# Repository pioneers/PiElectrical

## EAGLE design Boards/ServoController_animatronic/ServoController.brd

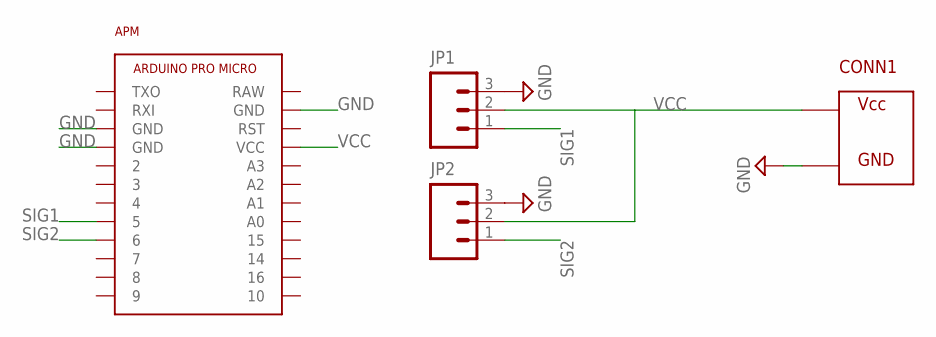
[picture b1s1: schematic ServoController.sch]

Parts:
APM: ARDUINO_PRO_MICRO
CONN1: ATX
JP1, JP2: M031X03-MTA; 1X03-MTA

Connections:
GND: APM.GND@0 (GND), APM.GND@1 (GND), APM.GND@2 (GND), CONN1.P$2, JP1.3, JP2.3
SIG1: APM.5, JP1.1
SIG2: APM.6, JP2.1
VCC: APM.VCC, CONN1.P$1, JP1.2, JP2.2

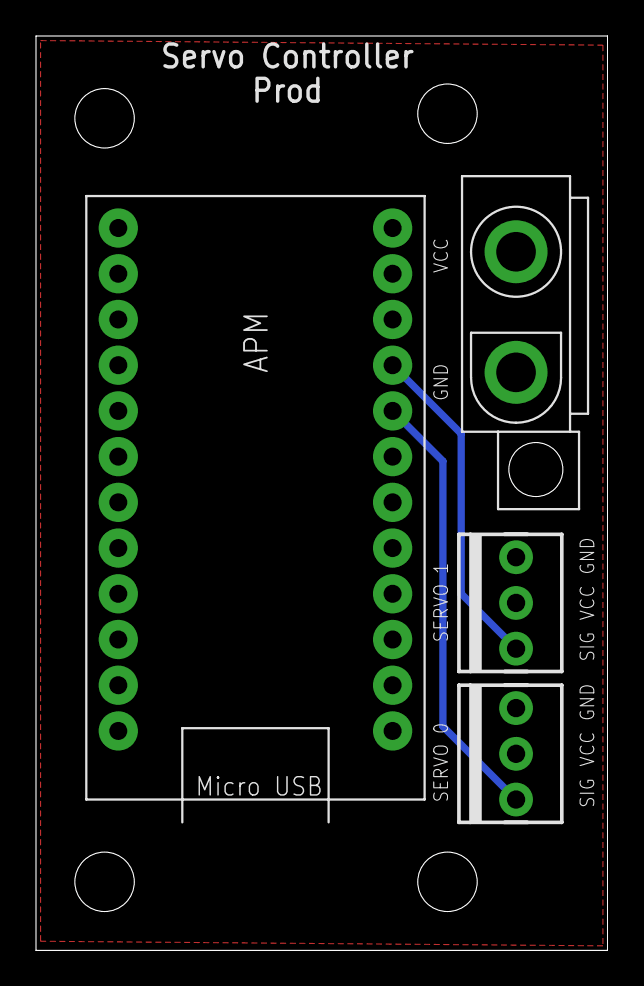
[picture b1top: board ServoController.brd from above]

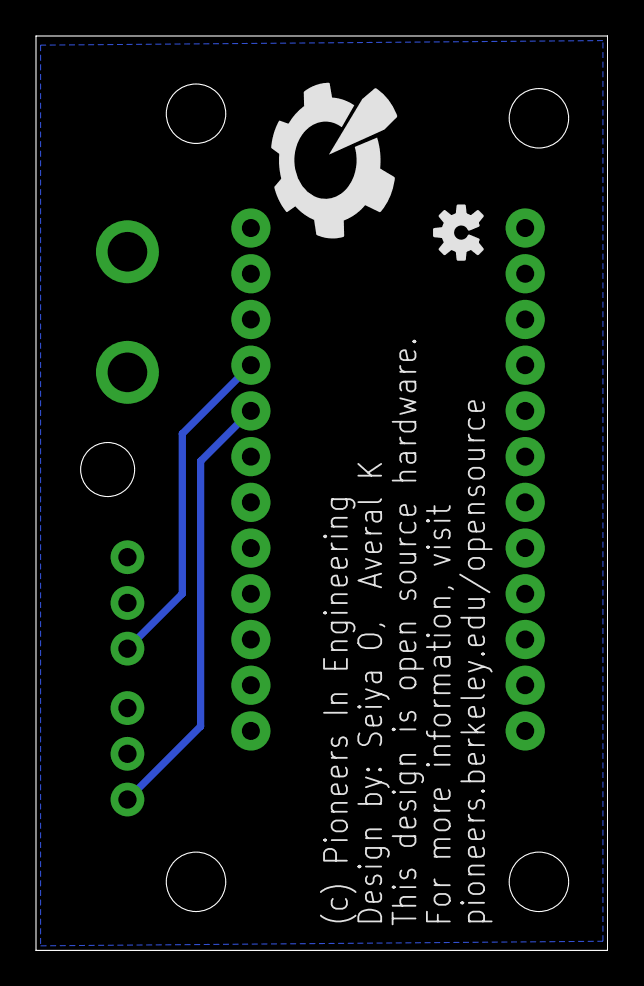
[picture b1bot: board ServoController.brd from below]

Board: 2 copper layers, 31.8 x 50.8 mm, 10 parts (2 on the bottom side), 4 nets.

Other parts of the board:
U$1, U$3, U$4, U$5: STAND-OFF
U$2: PIE-LOGO-SMALL
U$6: OSHW-LOGO-S

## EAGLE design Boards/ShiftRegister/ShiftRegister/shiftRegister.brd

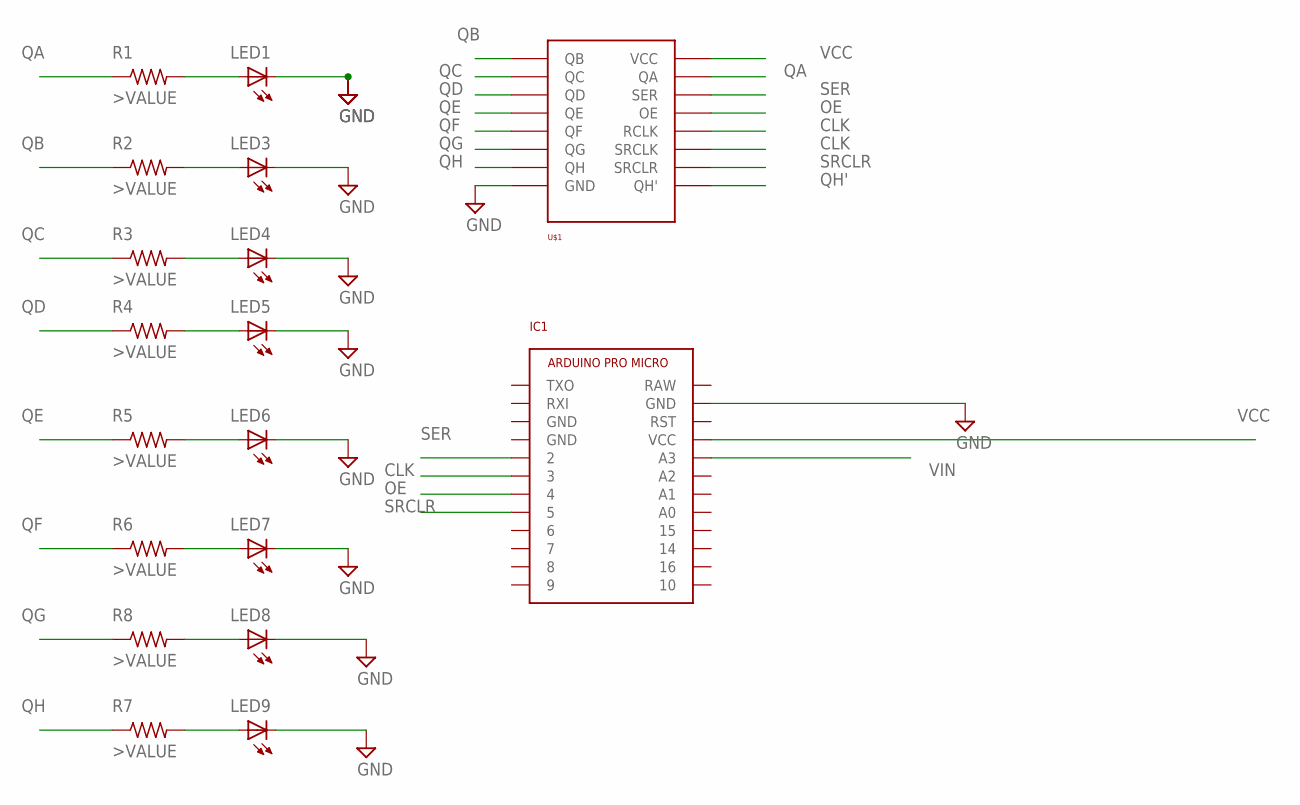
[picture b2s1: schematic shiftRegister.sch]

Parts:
IC1: ARDUINO_PRO_MICRO
LED1, LED3, LED4, LED5, LED6, LED7, LED8, LED9: LED-FKIT-1206; FKIT-LED-1206
R1, R2, R3, R4, R5, R6, R7, R8: >VALUE; R0603
U$1: SN74HC595

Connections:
CLK: IC1.3, U$1.RCLK, U$1.SRCLK
GND: IC1.GND@2 (GND), LED1.C, LED3.C, LED4.C, LED5.C, LED6.C, LED7.C, LED8.C, LED9.C, U$1.GND
unnamed: LED1.A, R1.2
unnamed: LED3.A, R2.2
unnamed: LED4.A, R3.2
unnamed: LED5.A, R4.2
unnamed: LED6.A, R5.2
unnamed: LED7.A, R6.2
unnamed: LED8.A, R8.2
unnamed: LED9.A, R7.2
OE: IC1.4, U$1.OE
QA: R1.1, U$1.QA
QB: R2.1, U$1.QB
QC: R3.1, U$1.QC
QD: R4.1, U$1.QD
QE: R5.1, U$1.QE
QF: R6.1, U$1.QF
QG: R8.1, U$1.QG
QH: R7.1, U$1.QH
QH': U$1.QH'
SER: IC1.2, U$1.SER
SRCLR: IC1.5, U$1.SRCLR
VCC: IC1.VCC, U$1.VCC
VIN: IC1.A3

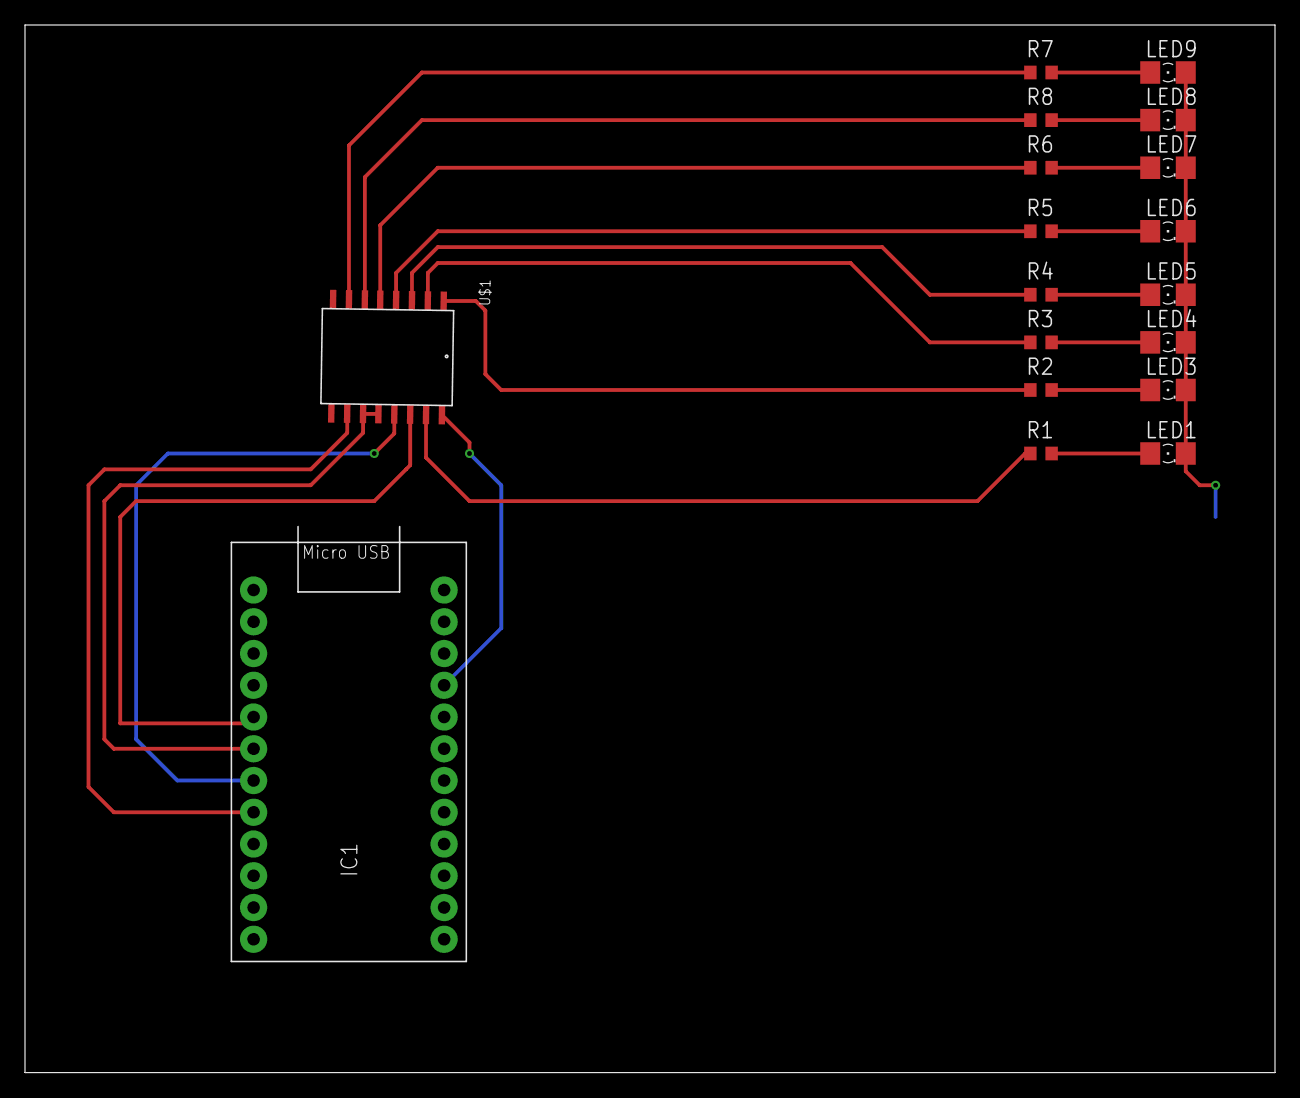
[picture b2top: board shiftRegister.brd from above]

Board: 2 copper layers, 100.0 x 83.8 mm, 18 parts (0 on the bottom side), 22 nets.

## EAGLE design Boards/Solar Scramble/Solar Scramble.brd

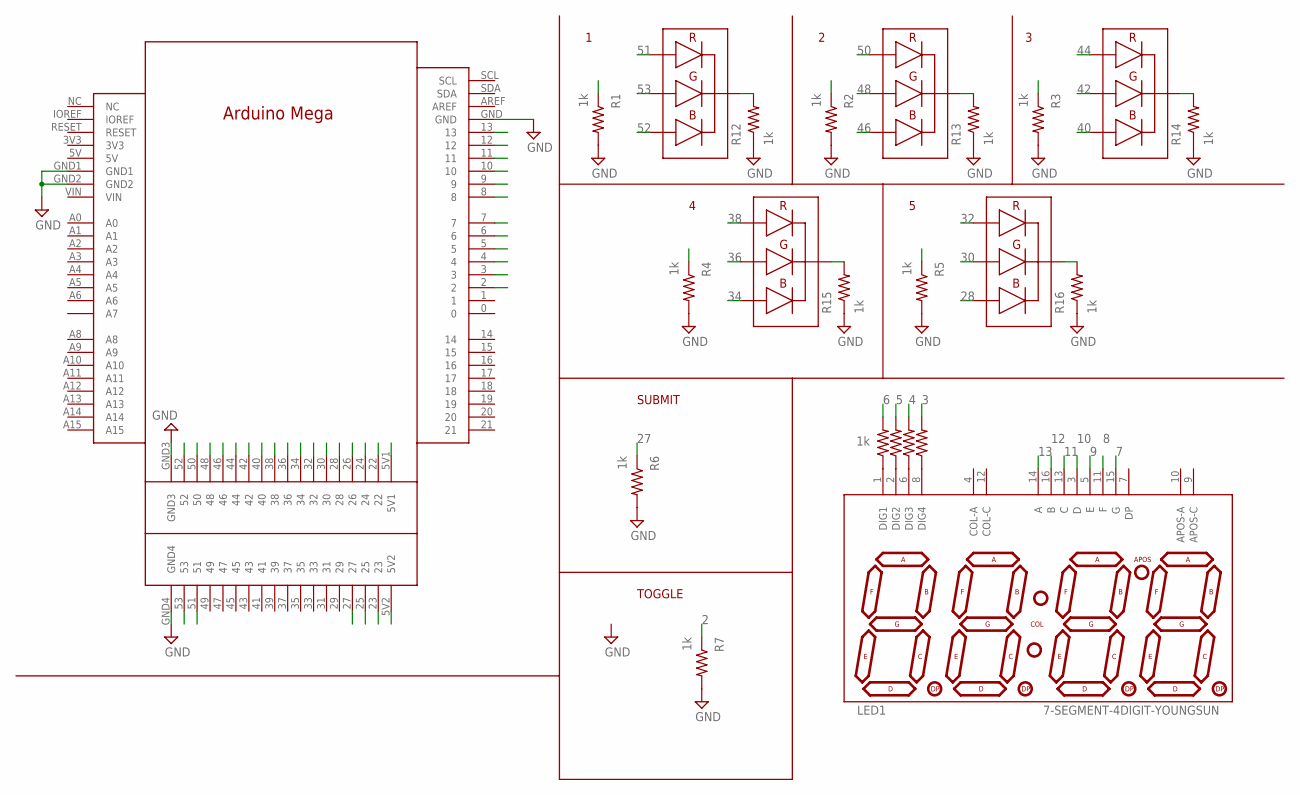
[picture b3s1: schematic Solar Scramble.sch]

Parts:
LED1: 7-SEGMENT-4DIGIT-YOUNGSUN
R1, R2, R3, R4, R5, R6, R7, R9, R10, R11, R12, R13, R14, R15, R16: 1k; R0603
R8: 1ik; R0603
U$1: ARD_MEGA
U$2, U$3, U$4, U$5, U$6: TRI-LED

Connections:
2: R7.1, U$1.2
3: R11.2, U$1.3
4: R10.2, U$1.4
5: R9.2, U$1.5
5V: U$1.5V1, U$1.5V2
6: R8.2, U$1.6
7: LED1.15 (G), U$1.7
8: LED1.11 (F), U$1.8
9: LED1.5 (E), U$1.9
10: LED1.3 (D), U$1.10
11: LED1.13 (C), U$1.11
12: LED1.16 (B), U$1.12
13: LED1.14 (A), U$1.13
22: R1.1, U$1.22
23: R2.1, U$1.23
24: R3.1, U$1.24
25: R4.1, U$1.25
26: R5.1, U$1.26
27: R6.1, U$1.27
28: U$1.28, U$5.B
30: U$1.30, U$5.G
32: U$1.32, U$5.R
34: U$1.34, U$4.B
36: U$1.36, U$4.G
38: U$1.38, U$4.R
40: U$1.40, U$3.B
42: U$1.42, U$3.G
44: U$1.44, U$3.R
46: U$1.46, U$6.B
48: U$1.48, U$6.G
50: U$1.50, U$6.R
51: U$1.51, U$2.R
52: U$1.52, U$2.B
53: U$1.53, U$2.G
GND: R1.2, R2.2, R3.2, R4.2, R5.2, R6.2, R7.2, R12.1, R13.1, R14.1, R15.1, R16.1, U$1.GND, U$1.GND1, U$1.GND2, U$1.GND3, U$1.GND4
unnamed: R15.2, U$4.GND (CAT)
unnamed: R12.2, U$2.GND (CAT)
unnamed: LED1.1 (DIG1), R8.1
unnamed: LED1.2 (DIG2), R9.1
unnamed: LED1.6 (DIG3), R10.1
unnamed: LED1.8 (DIG4), R11.1
unnamed: R13.2, U$6.GND (CAT)
unnamed: R14.2, U$3.GND (CAT)
unnamed: R16.2, U$5.GND (CAT)

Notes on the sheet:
SUBMIT
TOGGLE

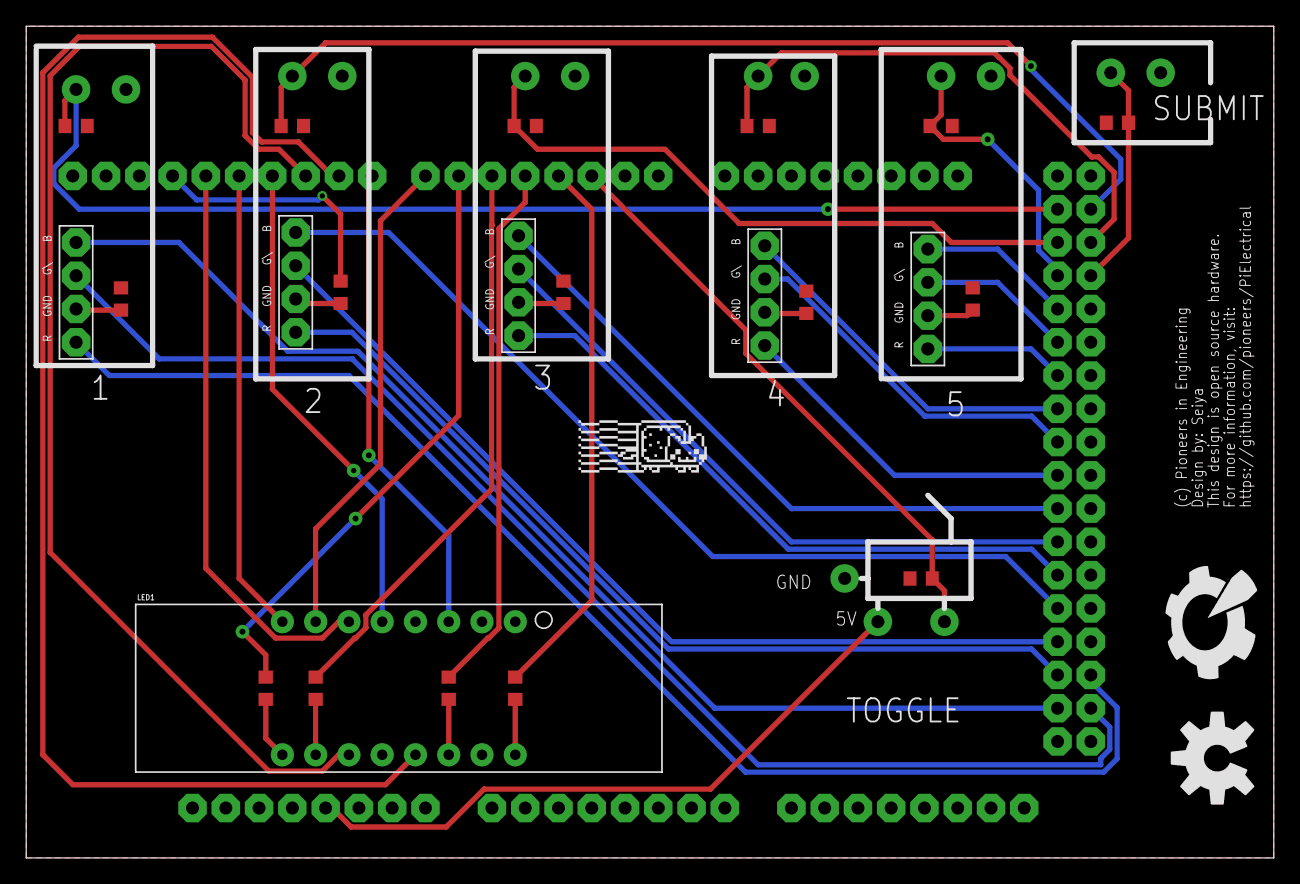
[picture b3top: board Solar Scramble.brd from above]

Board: 2 copper layers, 95.2 x 63.5 mm, 26 parts (0 on the bottom side), 44 nets.

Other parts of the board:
U$7: NYAN-1CM
U$8: OSHW-LOGO-L
U$9: PIE-LOGO-SMALL

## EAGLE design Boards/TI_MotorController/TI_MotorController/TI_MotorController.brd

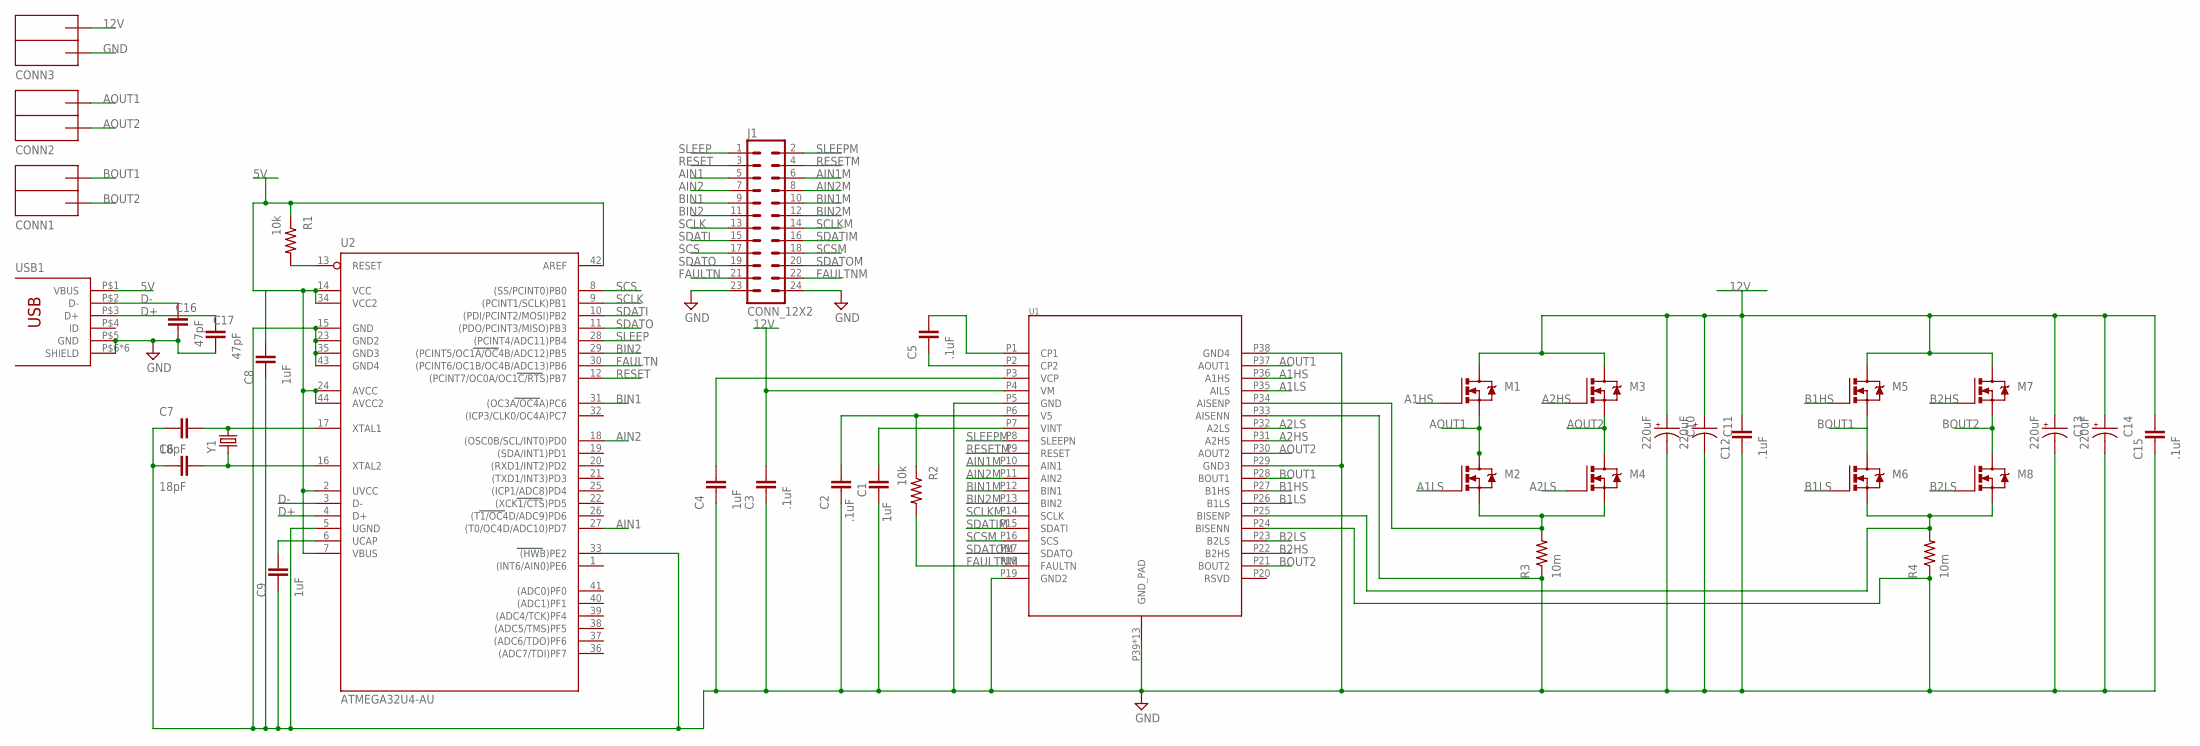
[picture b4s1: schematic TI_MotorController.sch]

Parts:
C1, C4, C8, C9: 1uF; 0603-CAP
C2, C3, C5, C12, C15: .1uF; 0603-CAP
C6, C7: 18pF; 0603-CAP
C10, C11, C13, C14: 220uF; NIPPON_F80
C16, C17: 47pF; 0603-CAP
CONN1, CONN2, CONN3: ANDERSONVERTICAL; ANDERSON_VERTICAL
J1: CONN_12X2; 2X12
M1, M2, M3, M4, M5, M6, M7, M8: NMOS_CSD17579Q3A; DNH0008A
R1, R2: 10k; R0603
R3, R4: 10m; R2512
U1: DRV8704; HTSSOP(38)
U2: ATMEGA32U4-AU; TQFP44
USB1: USB-OTGMICRO-AB; USB-MICRO-AB
Y1: CRYSTAL10.5X4.8; CRYSTAL-SMD-10.5X4.8-2PIN

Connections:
5V: C8.2, R1.1, U2.2 (UVCC), U2.7 (VBUS), U2.14 (VCC), U2.24 (AVCC), U2.34 (VCC2), U2.42 (AREF), U2.44 (AVCC2), USB1.P$1 (VBUS)
12V: C3.2, C10.+, C11.+, C12.2, C13.+, C14.+, C15.2, CONN3.PIN1 (OUTB), M1.5 (D), M1.6 (D), M1.7 (D), M1.8 (D), M1.9 (D), M3.5 (D), M3.6 (D), M3.7 (D), M3.8 (D), M3.9 (D), M5.5 (D), M5.6 (D), M5.7 (D), M5.8 (D), M5.9 (D), M7.5 (D), M7.6 (D), M7.7 (D), M7.8 (D), M7.9 (D), U1.P4 (VM)
A1HS: M1.4 (G), U1.P36 (A1HS)
A1LS: M2.4 (G), U1.P35 (AILS)
A2HS: M3.4 (G), U1.P31 (A2HS)
A2LS: M4.4 (G), U1.P32 (A2LS)
AIN1: J1.5, U2.27 ((T0/OC4D/ADC10)PD7)
AIN1M: J1.6, U1.P10 (AIN1)
AIN2: J1.7, U2.18 ((OSC0B/SCL/INT0)PD0)
AIN2M: J1.8, U1.P11 (AIN2)
AOUT1: CONN2.PIN1 (OUTB), M1.1 (S), M1.2 (S), M1.3 (S), M2.5 (D), M2.6 (D), M2.7 (D), M2.8 (D), M2.9 (D), U1.P37 (AOUT1)
AOUT2: CONN2.PIN2 (OUTA), M3.1 (S), M3.2 (S), M3.3 (S), M4.5 (D), M4.6 (D), M4.7 (D), M4.8 (D), M4.9 (D), U1.P30 (AOUT2)
B1HS: M5.4 (G), U1.P27 (B1HS)
B1LS: M6.4 (G), U1.P26 (B1LS)
B2HS: M7.4 (G), U1.P22 (B2HS)
B2LS: M8.4 (G), U1.P23 (B2LS)
BIN1: J1.9, U2.31 ((OC3A/OC4A)PC6)
BIN1M: J1.10, U1.P12 (BIN1)
BIN2: J1.11, U2.29 ((PCINT5/OC1A/OC4B/ADC12)PB5)
BIN2M: J1.12, U1.P13 (BIN2)
BOUT1: CONN1.PIN1 (OUTB), M5.1 (S), M5.2 (S), M5.3 (S), M6.5 (D), M6.6 (D), M6.7 (D), M6.8 (D), M6.9 (D), U1.P28 (BOUT1)
BOUT2: CONN1.PIN2 (OUTA), M7.1 (S), M7.2 (S), M7.3 (S), M8.5 (D), M8.6 (D), M8.7 (D), M8.8 (D), M8.9 (D), U1.P21 (BOUT2)
D+: C17.2, U2.4 (D+), USB1.P$3 (D+)
D-: C16.2, U2.3 (D-), USB1.P$2 (D-)
FAULTN: J1.21, U2.30 ((PCINT6/OC1B/OC4B/ADC13)PB6)
FAULTNM: J1.22, R2.2, U1.P18 (FAULTN)
GND: C1.1, C2.1, C3.1, C4.1, C6.1, C7.1, C8.1, C9.1, C10.-, C11.-, C12.1, C13.-, C14.-, C15.1, C16.1, C17.1, CONN3.PIN2 (OUTA), J1.23, J1.24, R3.1, R4.1, U1.P5 (GND), U1.P19 (GND2), U1.P24 (BISENN), U1.P29 (GND3), U1.P33 (AISENN), U1.P38 (GND4), U1.P39 (GND_PAD), U1.P40 (GND_PAD), U1.P41 (GND_PAD), U1.P42 (GND_PAD), U1.P43 (GND_PAD), U1.P44 (GND_PAD), U1.P45 (GND_PAD), U1.P46 (GND_PAD), U1.P47 (GND_PAD), U1.P48 (GND_PAD), U1.P49 (GND_PAD), U1.P50 (GND_PAD), U1.P51 (GND_PAD), U2.5 (UGND), U2.15 (GND), U2.23 (GND2), U2.33 ((HWB)PE2), U2.35 (GND3), U2.43 (GND4), USB1.P$5 (GND), USB1.P$6 (SHIELD), USB1.P$7 (SHIELD), USB1.P$8 (SHIELD), USB1.P$9 (SHIELD), USB1.P$10 (SHIELD), USB1.P$11 (SHIELD)
unnamed: C1.2, U1.P7 (VINT)
unnamed: C2.2, R2.1, U1.P6 (V5)
unnamed: R1.2, U2.13 (RESET)
unnamed: C4.2, U1.P3 (VCP)
unnamed: C5.1, U1.P2 (CP2)
unnamed: C5.2, U1.P1 (CP1)
unnamed: C7.2, U2.17 (XTAL1), Y1.P$2 (2)
unnamed: C6.2, U2.16 (XTAL2), Y1.P$1 (1)
unnamed: C9.2, U2.6 (UCAP)
unnamed: M2.1 (S), M2.2 (S), M2.3 (S), M4.1 (S), M4.2 (S), M4.3 (S), R3.2, U1.P34 (AISENP)
unnamed: M6.1 (S), M6.2 (S), M6.3 (S), M8.1 (S), M8.2 (S), M8.3 (S), R4.2, U1.P25 (BISENP)
RESET: J1.3, U2.12 ((PCINT7/OC0A/OC1C/RTS)PB7)
RESETM: J1.4, U1.P9 (RESET)
SCLK: J1.13, U2.9 ((PCINT1/SCLK)PB1)
SCLKM: J1.14, U1.P14 (SCLK)
SCS: J1.17, U2.8 ((SS/PCINT0)PB0)
SCSM: J1.18, U1.P16 (SCS)
SDATI: J1.15, U2.10 ((PDI/PCINT2/MOSI)PB2)
SDATIM: J1.16, U1.P15 (SDATI)
SDATO: J1.19, U2.11 ((PDO/PCINT3/MISO)PB3)
SDATOM: J1.20, U1.P17 (SDATO)
SLEEP: J1.1, U2.28 ((PCINT4/ADC11)PB4)
SLEEPM: J1.2, U1.P8 (SLEEPN)

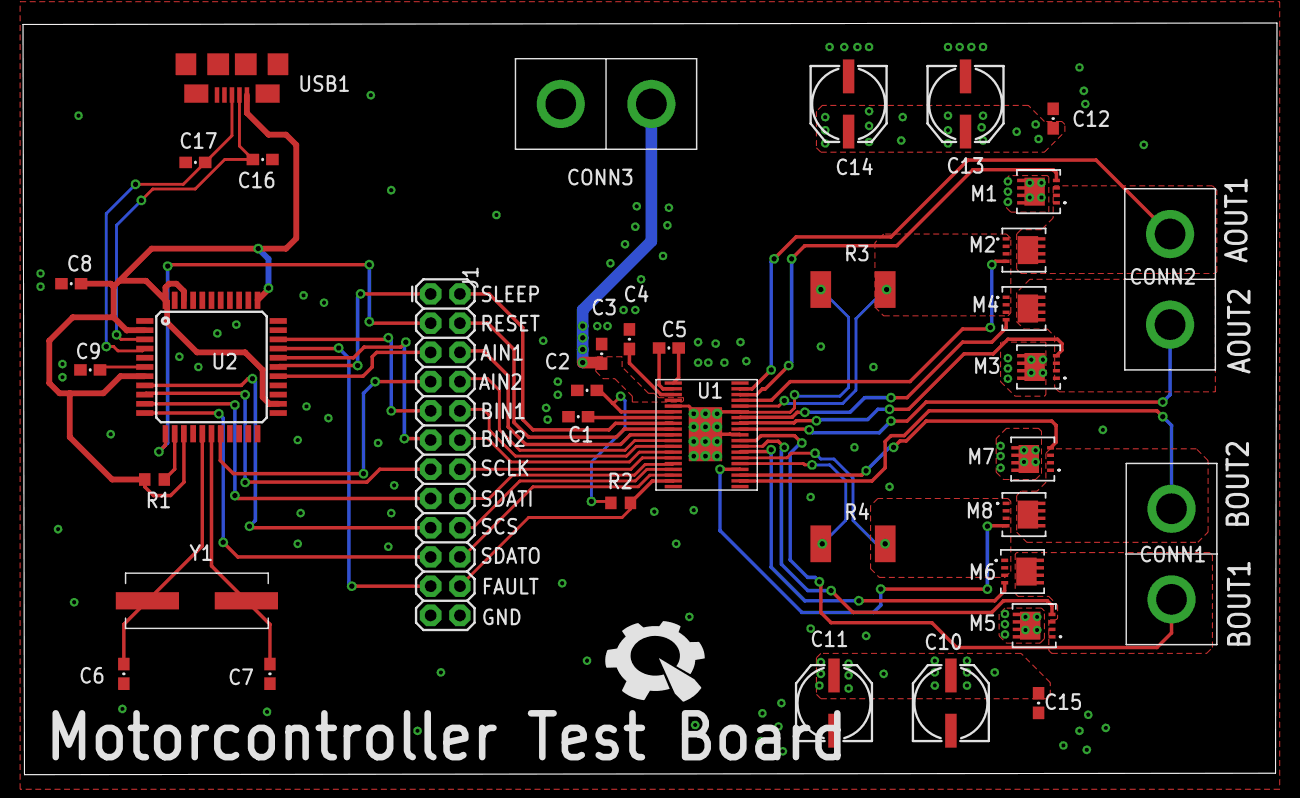
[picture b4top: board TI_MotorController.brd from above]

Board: 2 copper layers, 109.0 x 65.3 mm, 38 parts (0 on the bottom side), 50 nets.

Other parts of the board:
U$1: PIE-LOGO-SMALL

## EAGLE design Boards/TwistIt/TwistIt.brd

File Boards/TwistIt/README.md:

# TwistIt

Screw terminal based potentiometer/line follower/limit switch ultimate board

Named TwistIt for the screw terminal (open to suggestions)

Digital in Pins are all labeled "Arduino" in the pinout diagram

Analog pins are labeled as such

Analog pins can be used as digital, NOT vice versa

[2 Pin](https://www.sparkfun.com/products/8432) [3 pin](https://www.sparkfun.com/products/8433)

## Reed switches

Basically when it is placed in a magnetic field, the switch closes.

There surface mounts and through hole variants, but generally they have the same working range

For more specs, please view the link below:

http://www.digikey.com/product-search/en/switches/magnetic-reed-switches/1114199

It can be bought from Digikey, Sparkfun, Aliexpress, Amazon.

[AliExpress](https://www.aliexpress.com/item/10pcs-KSK-1A-Reed-Switch-2x14mm-Green-Glass-Usually-Open-For-Sensors-100-Original/32424207994.html)

To test it, connect it in series with a resistor and take the input from the point between them.

A sample of a simple code is shown below:

```
int reed = 2;

int LED = 3;

void setup() {

Serial.begin(9600);

pinMode(reed,INPUT);

pinMode(LED,OUTPUT);

}

void loop() {

if(digitalRead(reed)==HIGH){

digitalWrite(LED, HIGH);

}

else digitalWrite(3, LOW);

}
```
where an LED is attached to pin 3.

## Yogi Bear Break Out

VNH2SP30 | APM
-------- | ---
5V | Vcc
GND | GND
EN | 14
INA | 16
INB | 10
CS | 8
PMW | 9
Encoder A | 2
Encoder B | 3
Red | 4
Yellow | 5
Green | 6

[New Motor 1](https://e-smotor.en.alibaba.com/product/60220884310-801307434/37GB_spur_gear_motor_with_encoder.html?spm=a2700.7803228.1998738836.575.wFZGi0)

[New Motor 2](https://jslmotor.en.alibaba.com/product/60311538644-211952029/12v_24v_Pure_Metal_JGB37_3530B_Permanent_Magnet_High_Torque_24_Volt_Dc_Motor.html?spm=a2700.7803228.1998738836.185.6lh84F)

[Hardware Interrupts](https://www.arduino.cc/en/Reference/AttachInterrupt)

Encoder is all digital. A and B Out need to be pulled up and needs to be mapped to interrupt pins

Y9: The passive sensors worked great. The screw terminals were a great change that the students really liked. However, the line follow had issues b/c each signal was pulling up eachother.  However, the line following sensors didn't need pullups at all in the first place.  This could be fixed by not soldering in the pullup resistors.

Also the motor controller has to move a bit to make mounting a bit easier. At a minimum, move the yogibear pins .1" to the right, that *should* be enough clearance to let both andersons on the yogibear stand straight up.  Additionally, the encoder connector should be moved to the right side (current on left) of the PCB, since that is the location closest to the motors. 

Also pullups (on the encoders). Thanks pullups.

Y10: Somebody

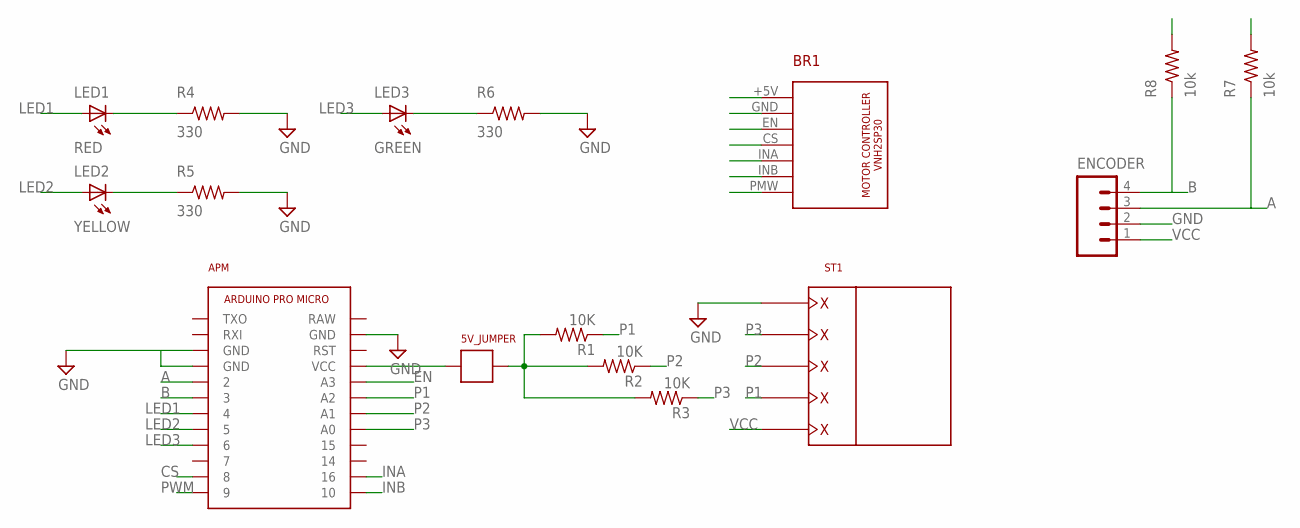
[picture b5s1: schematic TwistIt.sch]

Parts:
5V_JUMPER: JUMPER
APM: ARDUINO_PRO_MICRO
BR1: VNH2SP30_MOTOR_CONTROLLER
ENCODER: M041X04-MTA; 1X04-MTA
LED1: RED; LED-1206
LED2: YELLOW; LED-1206
LED3: GREEN; LED-1206
R1, R2, R3: 10K; R0603
R4, R5, R6: 330; R0603
R7, R8: 10k; R0603
ST1: 5PIN_SCREW

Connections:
5V: 5V_JUMPER.P$2, R1.2, R2.2, R3.2
A: APM.2, ENCODER.3, R7.1
B: APM.3, ENCODER.4, R8.1
CS: APM.8, BR1.CS
EN: APM.A3, BR1.EN
GND: APM.GND@0 (GND), APM.GND@1 (GND), APM.GND@2 (GND), BR1.GND, ENCODER.2, R4.2, R5.2, R6.2, ST1.P$1
INA: APM.16, BR1.INA
INB: APM.10, BR1.INB
LED1: APM.4, LED1.A
LED2: APM.5, LED2.A
LED3: APM.6, LED3.A
unnamed: LED1.C, R4.1
unnamed: LED2.C, R5.1
unnamed: LED3.C, R6.1
P1: APM.A2, R1.1, ST1.P$4
P2: APM.A1, R2.1, ST1.P$3
P3: APM.A0, R3.1, ST1.P$2
PWM: APM.9, BR1.PMW (PWM)
VCC: 5V_JUMPER.P$1, APM.VCC, BR1.+5V, ENCODER.1, R7.2, R8.2, ST1.P$5

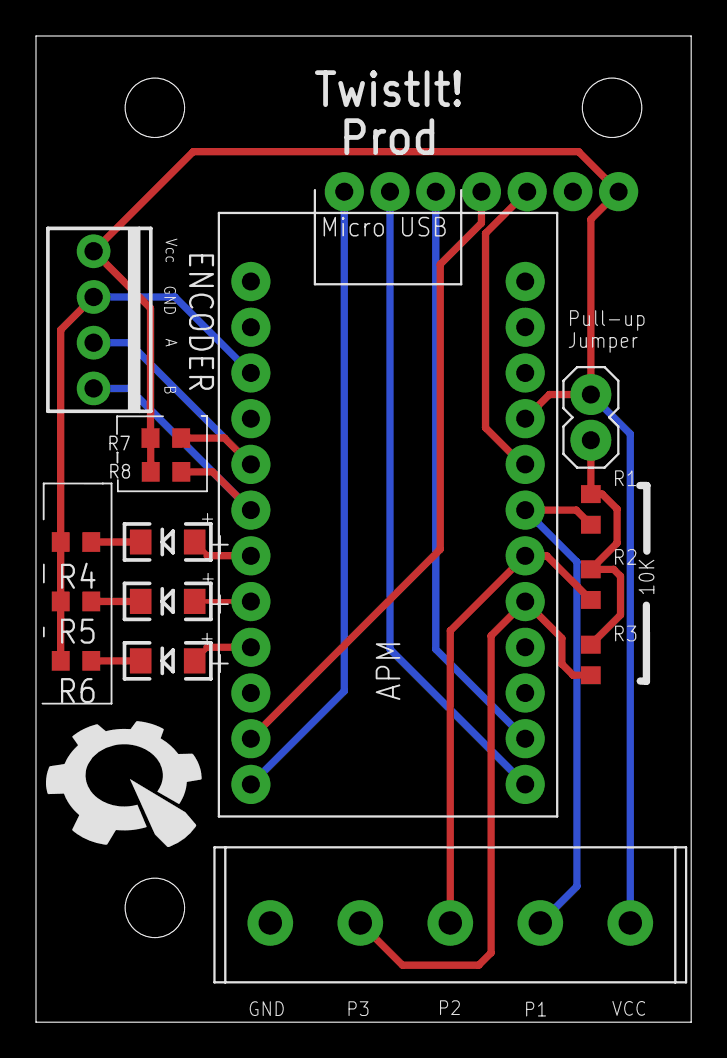
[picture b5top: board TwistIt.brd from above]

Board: 2 copper layers, 36.4 x 54.8 mm, 21 parts (1 on the bottom side), 19 nets.

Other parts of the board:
U$1, U$5, U$6: STAND-OFF
U$3: PIE-LOGO-SMALL
U$4: OSHW-LOGO-S

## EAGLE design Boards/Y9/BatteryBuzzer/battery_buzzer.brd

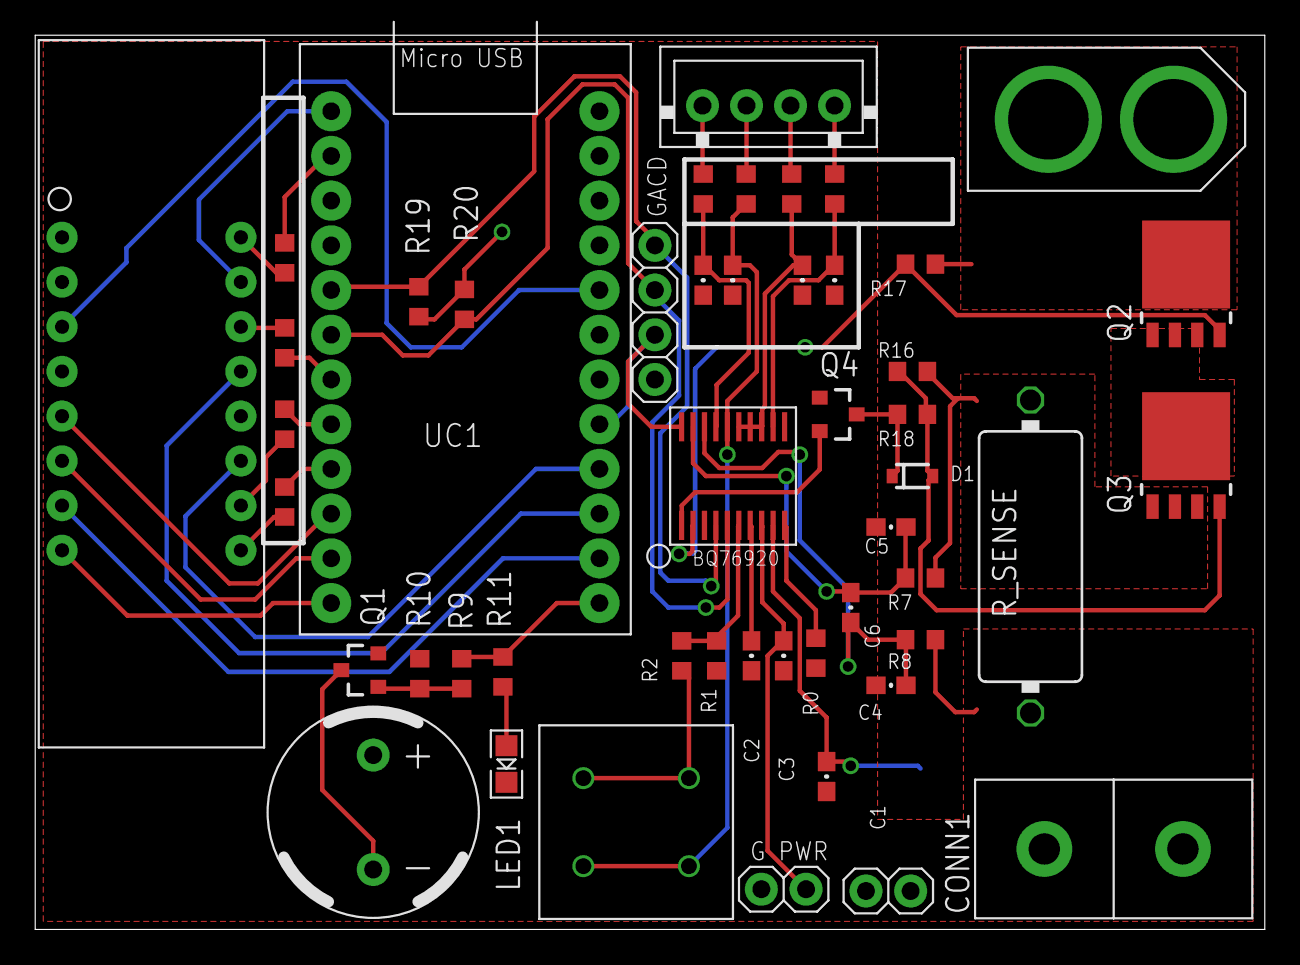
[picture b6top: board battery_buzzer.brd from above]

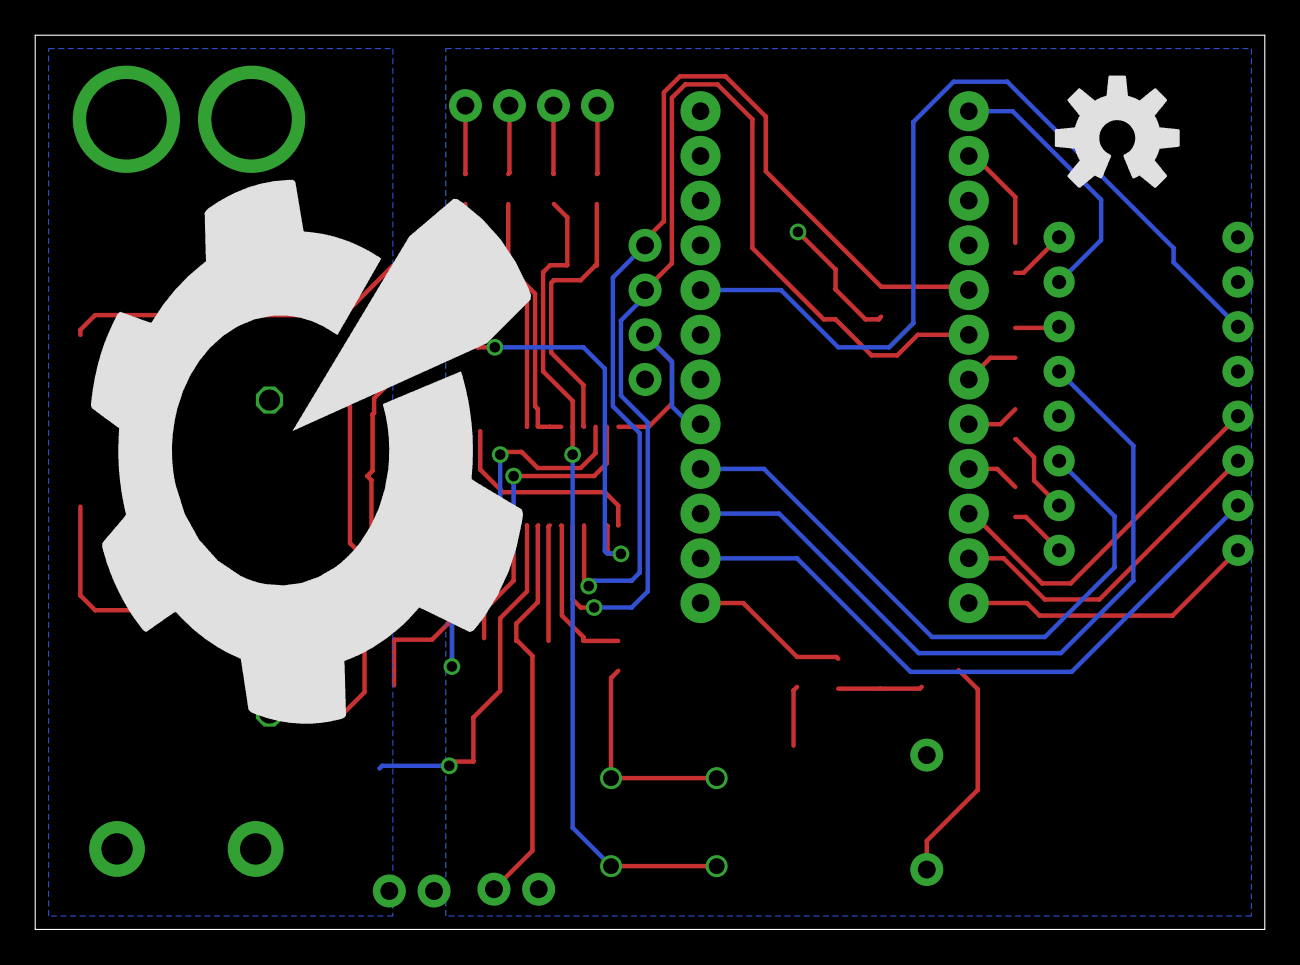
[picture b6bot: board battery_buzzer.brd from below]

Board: 2 copper layers, 69.8 x 50.8 mm, 51 parts (2 on the bottom side), 48 nets.

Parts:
C1, C2, C7, C8, C9, C10: 1uF; 0603-CAP
C3: 4.7uF; 0603-CAP
C4, C5, C6: .1uF; 0603-CAP
CONN1: ANDERSONVERTICAL; ANDERSON_VERTICAL
D1: SOD-323
JP1: XH_CONN; XH_CONNECTOR_4POS_2.5MM
JP2, JP4: 1X02
JP3: 1X04
LED1: RED; LED-0805
LED2: 7-SEGMENT; 7-SEGMENT-4DIGIT-YOUNGSUN
LS1: BUZZER; BUZZER_MAGNETIC_5V_12MM_RADIAL
Q1: IRFML8244; SOT23-3
Q2, Q3: N-CHANNEL-MOSFETSOT669; SOT669
Q4: P-CHANNEL-MOSFETSOT23-3; SOT23-3
R0, R3, R4, R5, R6, R7, R8, R9, R18: 100; R0603
R1, R19, R20: 1k; R0603
R2, R10: 10k; R0603
R11: 130; R0603
R12, R13, R14, R15: 330; R0603
R16, R17: 1M; R0603
R_SENSE: 0.008; V235/17
S1: DPST_SWITCH; C&K_SWITCH
U1: BQ76920; 20-TSSOP
U$1: XT60CONNECTOR
U$2: OSHW-LOGO-L
U$4: PIE-LOGO
UC1: ARDUINO_PRO_MICRO

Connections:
5V: LS1.A, R19.1, R20.1, UC1.VCC
A: LED2.14, UC1.8
ALERT: JP3.3, U1.P$20, UC1.A0
B: LED2.16, UC1.9
BCELL1: C9.1, R4.1, S1.P1', S1.P2', U1.P$16
BCELL2: C8.1, R5.1, U1.P$13, U1.P$14, U1.P$15
BCELL3: C7.2, R6.1, U1.P$12
BGND: C10.1, R3.1, U1.P$17
BUZZER_SIGNAL: R9.1, R11.2, UC1.10
C: LED2.13, UC1.7
CHG: Q2.4, R17.2, U1.P$2
D: LED2.3, UC1.15
DIG_1: R12.2, UC1.6
DIG_2: R13.2, UC1.5
DIG_3: R14.2, UC1.4
DIG_4: R15.2, UC1.RXI
DP: LED2.7, UC1.TXO
DSG: Q4.2, U1.P$1
E: LED2.5, UC1.14
F: LED2.11, UC1.A3
G: LED2.15, UC1.16
GND: C1.1, C2.1, C3.1, C4.2, C5.1, C7.1, C8.2, C9.2, C10.2, CONN1.PIN1, JP2.1, JP2.2, JP3.4, JP4.1, LED1.C, Q1.2, Q4.1, R0.2, R1.2, R8.1, R10.1, R_SENSE.2, U1.P$3, UC1.GND@0, UC1.GND@1, UC1.GND@2
unnamed: R0.1, U1.P$10
unnamed: C2.2, U1.P$7
unnamed: JP1.1, R3.2
unnamed: JP1.2, R4.2
unnamed: LS1.C, Q1.3
unnamed: Q1.1, R9.2, R10.2
unnamed: LED1.A, R11.1
unnamed: R2.1, S1.P1, S1.P2
unnamed: LED2.1, R12.1
unnamed: JP1.3, R5.2
unnamed: LED2.2, R13.1
unnamed: JP1.4, R6.2
unnamed: LED2.6, R14.1
unnamed: Q2.1, Q2.2, Q2.3, Q3.MB
unnamed: LED2.8, R15.1
unnamed: Q3.1, Q3.2, Q3.3, R7.1, R16.1, R_SENSE.1
unnamed: D1.1, Q4.3, R18.2
unnamed: D1.2, Q3.4, R16.2, R18.1
PACK+: C1.2, CONN1.PIN2, U1.P$9, U$1.12V
PACK-: Q2.MB, R17.1, U$1.GND
REGOUT: C3.2, JP4.2, U1.P$8
SCL: JP3.2, R20.2, U1.P$5, UC1.3
SDA: JP3.1, R19.2, U1.P$4, UC1.2
SRN: C5.2, C6.1, R7.2, U1.P$19
SRP: C4.1, C6.2, R8.2, U1.P$18
TS: R1.1, R2.2, U1.P$6

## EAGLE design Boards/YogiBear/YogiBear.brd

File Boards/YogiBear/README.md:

#YOGI BEAR

Yogi Bear is a cool bear.

[VNH2SP30](https://www.aliexpress.com/item/Free-shipping-VNH2SP30-in-stock/32235666194.html?spm=2114.01010208.3.154.pCpm6w&ws_ab_test=searchweb0_0,searchweb201602_4_10056_10065_10055_10068_10067_10054_10069_10059_418_10073_10017_10070_10060_10061_10052_10062_10053_10050_10051,searchweb201603_3&btsid=7e6b3cdb-1352-4e9c-9080-e427ead57444)

[MOSFET DIGI REEL] (http://www.digikey.com/product-detail/en/infineon-technologies/IPD90N03S4L-02/IPD90N03S4L-02DKR-ND/2231371)

[MOSFET CUT TAPE] (http://www.digikey.com/product-detail/en/infineon-technologies/IPD90N03S4L-02/IPD90N03S4L-02CT-ND/2231143)

Y9: Wasn't used

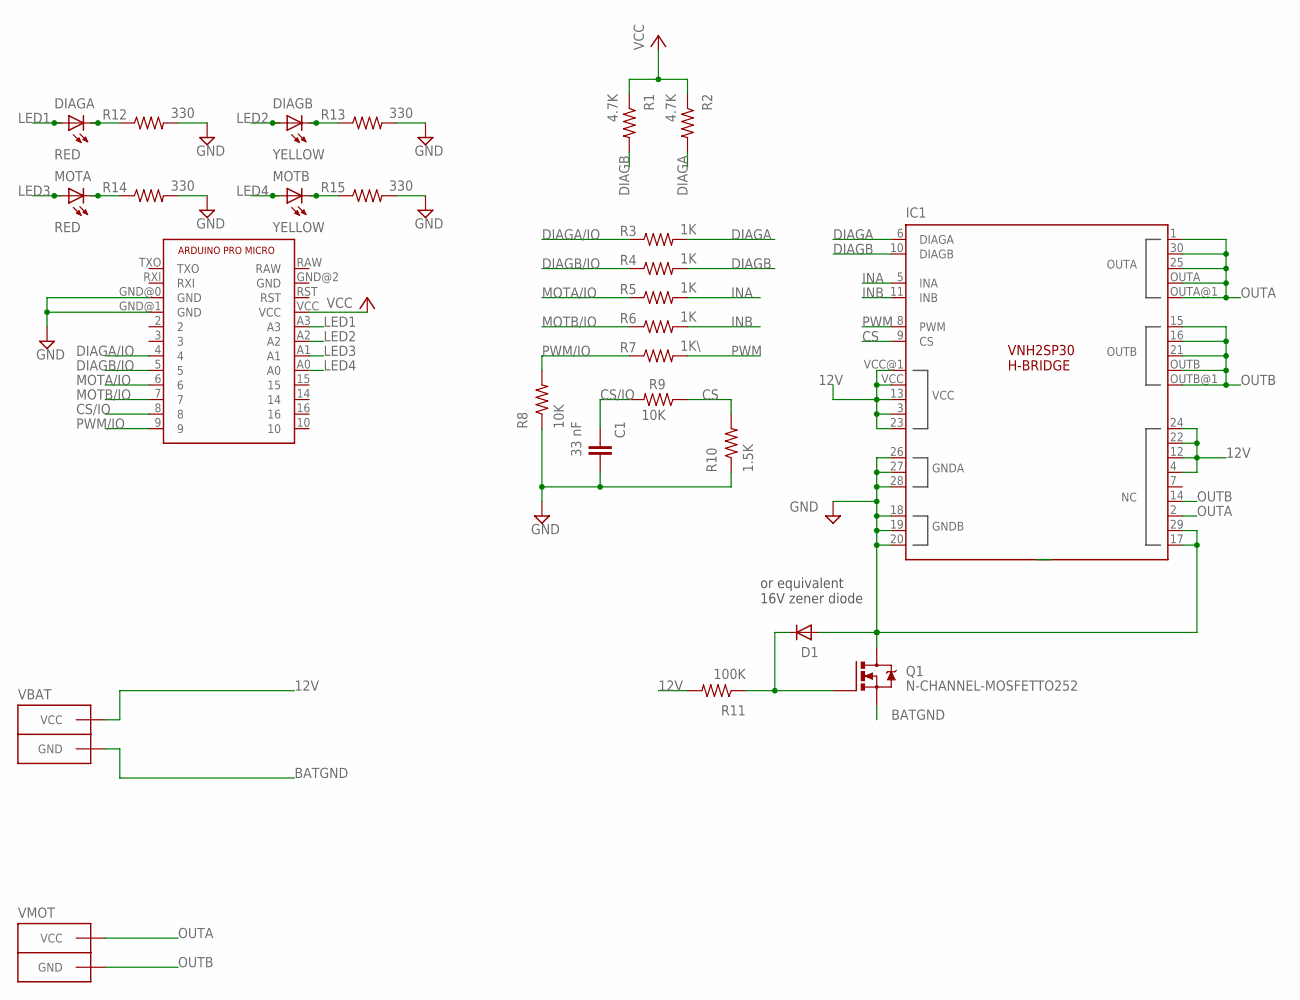
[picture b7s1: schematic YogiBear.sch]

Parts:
C1: 33 nF; 0603-CAP
D1: DIODESMA-ALT; SMA-DIODE_ALT
DIAGA: RED; LED-0603
DIAGB: YELLOW; LED-0603
IC1: VNH2SP30
MOTA: RED; LED-0603
MOTB: YELLOW; LED-0603
Q1: N-CHANNEL-MOSFETTO252; TO252
R1, R2: 4.7K; R0603
R3, R4, R5, R6: 1K; R0603
R7: 1K\; R0603
R8, R9: 10K; R0603
R10: 1.5K; R0603
R11: 100K; R0603
R12, R13, R14, R15: 330; R0603
U$1: ARDUINO_PRO_MICRO
VBAT: ANDERSONVERTICAL; ANDERSON_VERTICAL
VMOT: ANDERSONVERTICAL; ANDERSON_VERTICAL

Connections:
12V: IC1.3 (VCC), IC1.4 (NC5), IC1.12 (NC6), IC1.13 (VCC), IC1.22 (NC7), IC1.23 (VCC), IC1.24 (NC8), IC1.VCC, IC1.VCC@1 (VCC), R11.2, VBAT.PIN2 (VCC)
BATGND: Q1.2 (S), VBAT.PIN1 (GND)
CS: IC1.9 (CS), R9.1, R10.2
CS/IO: C1.1, R9.2, U$1.8
DIAGA: IC1.6 (DIAGA), R2.2, R3.2
DIAGA/IO: R3.1, U$1.4
DIAGB: IC1.10 (DIAGB), R1.2, R4.2
DIAGB/IO: R4.1, U$1.5
GND: C1.2, D1.A, IC1.17 (NC), IC1.18 (GNDB), IC1.19 (GNDB), IC1.20 (GNDB), IC1.26 (GNDA), IC1.27 (GNDA), IC1.28 (GNDA), IC1.29 (NC1), Q1.3 (D), R8.1, R10.1, R12.2, R13.2, R14.2, R15.2, U$1.GND@0 (GND), U$1.GND@1 (GND)
INA: IC1.5 (INA), R5.2
INB: IC1.11 (INB), R6.2
LED1: DIAGA.A, U$1.A3
LED2: DIAGB.A, U$1.A2
LED3: MOTA.A, U$1.A1
LED4: MOTB.A, U$1.A0
MOTA/IO: R5.1, U$1.6
MOTB/IO: R6.1, U$1.7
unnamed: D1.C, Q1.1 (G), R11.1
unnamed: MOTB.C, R15.1
unnamed: MOTA.C, R14.1
unnamed: DIAGB.C, R13.1
unnamed: DIAGA.C, R12.1
NC4: IC1.7 (NC4)
OUTA: IC1.1 (OUTA), IC1.2 (NC2), IC1.25 (OUTA), IC1.30 (OUTA), IC1.OUTA, IC1.OUTA@1 (OUTA), VMOT.PIN2 (VCC)
OUTB: IC1.14 (NC3), IC1.15 (OUTB), IC1.16 (OUTB), IC1.21 (OUTB), IC1.OUTB, IC1.OUTB@1 (OUTB), VMOT.PIN1 (GND)
PWM: IC1.8 (PWM), R7.2
PWM/IO: R7.1, R8.2, U$1.9
VCC: R1.1, R2.1, U$1.VCC

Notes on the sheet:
or equivalent 16V zener diode

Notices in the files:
parts and their libraries:
SparkFun-Connectors: Licensing: Creative Commons ShareAlike 4.0 International - https://creativecommons.org/licenses/by-sa/4.0
